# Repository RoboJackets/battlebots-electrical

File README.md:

BattleBots Electrical
=====================

Black Box Sensor
-----------
This folder has the design for a PCB that can measure kinematics during impact for testing combat robots.

Meltybrain
-----------
This folder contains the designs for PCBs for a combat robot that utilizes translational drift.

Motor Speed Testing
-------------------
This folder has code for graphing brushless motor spinup speed.

Safety LEDs
-----------
This folder has the design and code for a PCB for a safety LED controller for combat robots.

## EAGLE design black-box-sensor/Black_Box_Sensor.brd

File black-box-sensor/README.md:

Black-Box Sensor
=====================

This directory contains all design files for the Black-Box Sensor BattleBots project.  It is a sensor that will measure acceleration and jerk during collisions.

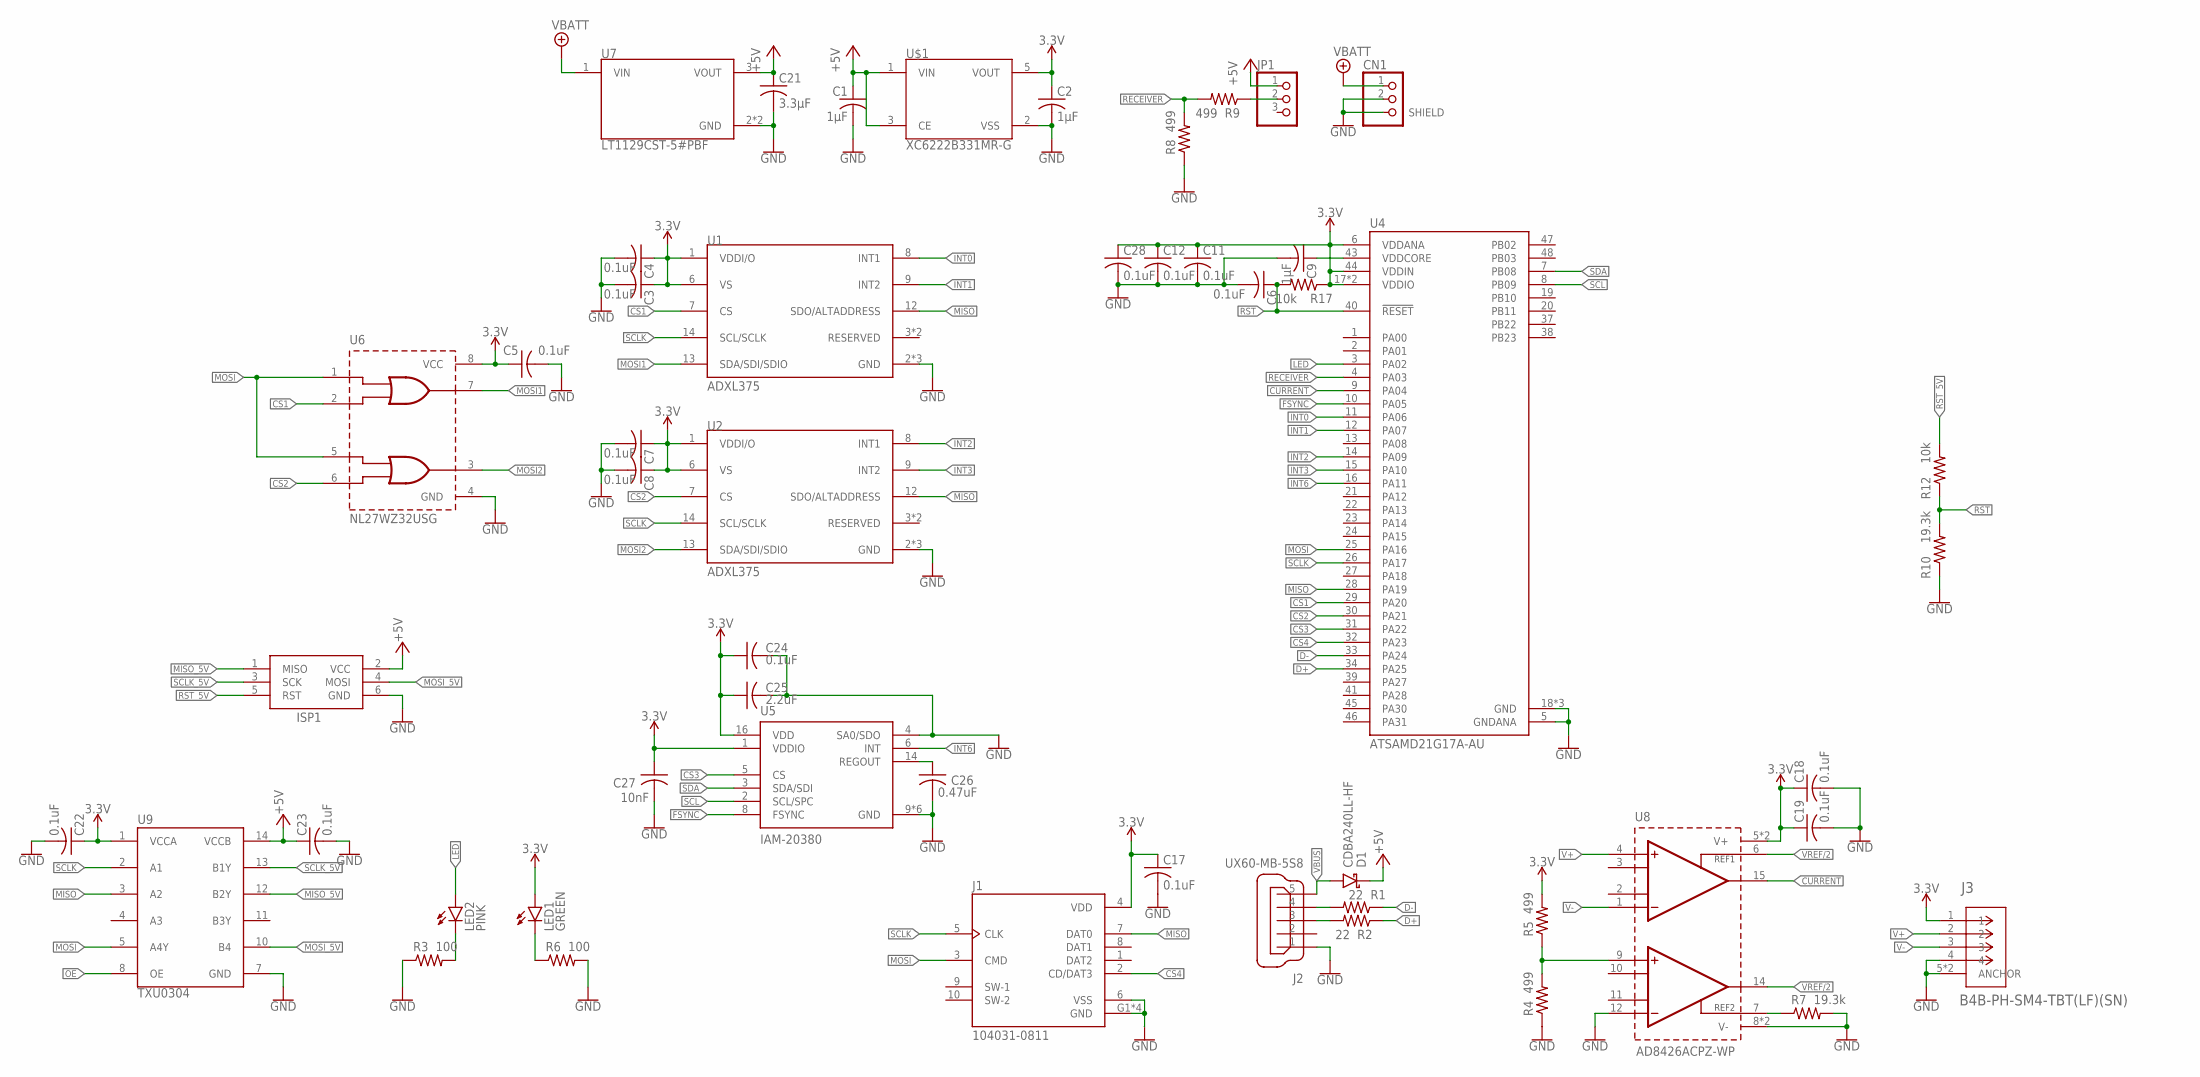
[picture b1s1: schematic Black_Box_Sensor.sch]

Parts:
C1, C2, C9: 1µF; C0603; VOLTAGE 10V
C3, C4, C5, C6, C7, C8, C11, C12, C17, C18, C19, C24, C28: 0.1uF; C0603
C21: 3.3µF; C0603; VOLTAGE 10V
C22, C23: 0.1uF; C0603K
C25: 2.2uF; C0603
C26: 0.47uF; C0603
C27: 10nF; C0603
CN1: JST_2PIN; JST-PH-2-SMT
D1: CDBA240LL-HF; DIOM5225X250N
ISP1: AVRISP-6; AVRISP
J1: 104031-0811; MOLEX_104031-0811
J2: UX60-MB-5S8
J3: B4B-PH-SM4-TBT(LF)(SN); CONN_B4B-PH-SM4-TB_JST
JP1: PINHD-1X3; 1X03
LED1: GREEN; CHIP-LED0805
LED2: PINK; KA-3528ASYC
R1, R2: 22; R0603
R3, R6: 100; R0603
R4, R5, R8, R9: 499; R0603
R7, R10: 19.3k; R0603
R12, R17: 10k; R0603
U1, U2: ADXL375; 14-VFLGA
U4: ATSAMD21G17A-AU; TQFP48
U5: IAM-20380; PQFN50P300X300X80-16N
U6: NL27WZ32USG; US8
U7: LT1129CST-5#PBF; SOT-223-3
U8: AD8426ACPZ-WP; 16LFCSP
U9: TXU0304; TSSOP14
U$1: XC6222B331MR-G; SOT-25

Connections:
3.3V: C2.1, C3.1, C4.1, C5.1, C7.1, C8.1, C11.1, C12.1, C17.1, C18.1, C19.1, C22.1, C24.1, C25.1, C27.1, C28.1, J1.4 (VDD), J3.1, LED1.A, R5.2, R17.1, U1.1 (VDDI/O), U1.6 (VS), U2.1 (VDDI/O), U2.6 (VS), U4.6 (VDDANA), U4.17 (VDDIO), U4.36 (VDDIO), U4.44 (VDDIN), U5.1 (VDDIO), U5.16 (VDD), U6.8 (VCC), U8.5 (V+), U8.16 (V+), U9.1 (VCCA), U$1.5 (VOUT)
+5V: C1.1, C21.1, C23.1, D1.C, JP1.1, U7.3 (VOUT), U9.14 (VCCB), U$1.1 (VIN), U$1.3 (CE)
CS1: U1.7 (CS), U4.29 (PA20), U6.2 (B1)
CS2: U2.7 (CS), U4.30 (PA21), U6.6 (B2)
CS3: U4.31 (PA22), U5.5 (CS)
CS4: J1.2 (CD/DAT3), U4.32 (PA23)
CURRENT: U4.9 (PA04), U8.15 (OUTA)
D+: R2.1, U4.34 (PA25)
D-: R1.1, U4.33 (PA24)
FSYNC: U4.10 (PA05), U5.8 (FSYNC)
GND: C1.2, C2.2, C3.2, C4.2, C5.2, C6.2, C7.2, C8.2, C9.2, C11.2, C12.2, C17.2, C18.2, C19.2, C21.2, C22.2, C23.2, C24.2, C25.2, C26.2, C27.2, C28.2, CN1.2, CN1.NC1 (SHIELD), CN1.NC2 (SHIELD), ISP1.6 (GND), J1.6 (VSS), J1.G1 (GND), J1.G2 (GND), J1.G3 (GND), J1.G4 (GND), J2.1, J3.4, J3.5 (ANCHOR), J3.6 (ANCHOR), R3.1, R4.1, R6.2, R7.2, R8.1, R10.1, U1.2 (GND), U1.4 (GND), U1.5 (GND), U2.2 (GND), U2.4 (GND), U2.5 (GND), U4.5 (GNDANA), U4.18 (GND), U4.35 (GND), U4.42 (GND), U5.4 (SA0/SDO), U5.9 (GND), U5.10 (GND), U5.11 (GND), U5.12 (GND), U5.13 (GND), U5.15 (GND), U6.4 (GND), U7.2 (GND), U7.4 (GND), U8.8 (V-), U8.12 (INB-), U8.13 (V-), U9.7 (GND), U$1.2 (VSS)
INT0: U1.8 (INT1), U4.11 (PA06)
INT1: U1.9 (INT2), U4.12 (PA07)
INT2: U2.8 (INT1), U4.14 (PA09)
INT3: U2.9 (INT2), U4.15 (PA10)
INT6: U4.16 (PA11), U5.6 (INT)
LED: LED2.A, U4.3 (PA02)
MISO: J1.7 (DAT0), U1.12 (SDO/ALTADDRESS), U2.12 (SDO/ALTADDRESS), U4.28 (PA19), U9.3 (A2)
MISO_5V: ISP1.1 (MISO), U9.12 (B2Y)
MOSI: J1.3 (CMD), U4.25 (PA16), U6.1 (A1), U6.5 (A2), U9.5 (A4Y)
MOSI1: U1.13 (SDA/SDI/SDIO), U6.7 (Y1)
MOSI2: U2.13 (SDA/SDI/SDIO), U6.3 (Y2)
MOSI_5V: ISP1.4 (MOSI), U9.10 (B4)
unnamed: C9.1, U4.43 (VDDCORE)
unnamed: J2.3, R2.2
unnamed: J2.4, R1.2
unnamed: R4.2, R5.1, U8.9 (INB+)
unnamed: LED2.C, R3.2
unnamed: LED1.C, R6.1
unnamed: JP1.2, R9.1
unnamed: R7.1, U8.7 (REFB)
unnamed: C26.1, U5.14 (REGOUT)
OE: U9.8 (OE)
RECEIVER: R8.2, R9.2, U4.4 (PA03)
RST: C6.1, R10.2, R12.1, R17.2, U4.40 (!RESET!)
RST_5V: ISP1.5 (RST), R12.2
SCL: U4.8 (PB09), U5.2 (SCL/SPC)
SCLK: J1.5 (CLK), U1.14 (SCL/SCLK), U2.14 (SCL/SCLK), U4.26 (PA17), U9.2 (A1)
SCLK_5V: ISP1.3 (SCK), U9.13 (B1Y)
SDA: U4.7 (PB08), U5.3 (SDA/SDI)
V+: J3.2, U8.4 (INA+)
V-: J3.3, U8.1 (INA-)
VBATT: CN1.1, U7.1 (VIN)
VBUS: D1.A, J2.5
VREF/2: U8.6 (REFA), U8.14 (OUTB)

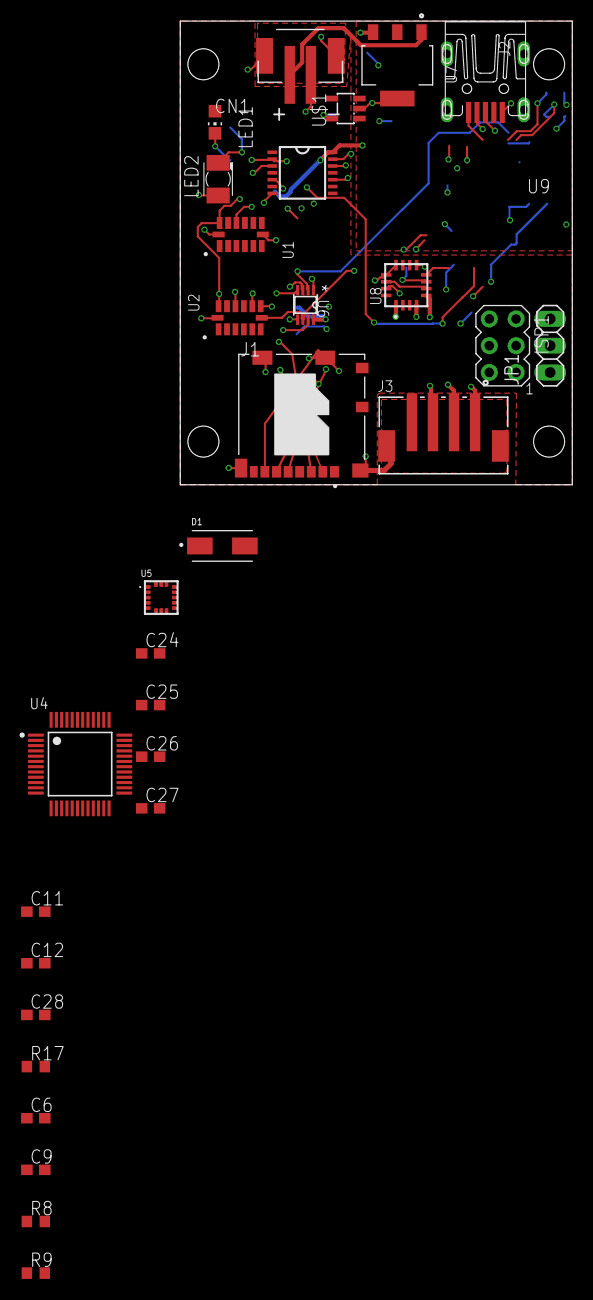
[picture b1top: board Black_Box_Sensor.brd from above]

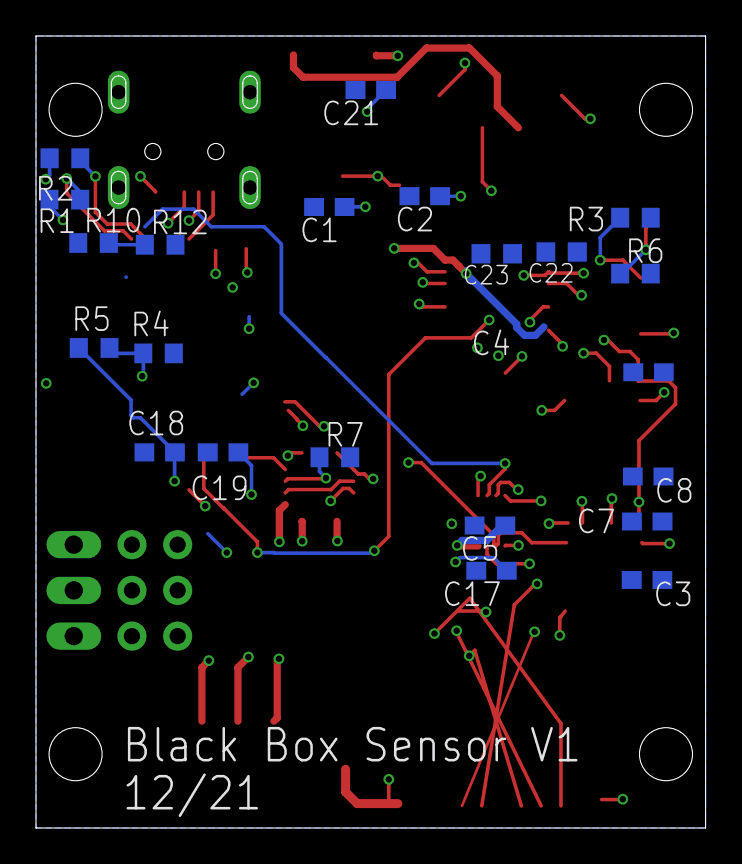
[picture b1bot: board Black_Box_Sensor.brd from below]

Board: 4 copper layers, 37.2 x 44.0 mm, 52 parts (22 on the bottom side), 44 nets.

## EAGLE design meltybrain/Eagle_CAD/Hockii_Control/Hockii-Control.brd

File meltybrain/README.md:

Meltybrain Electrical
=====================

This directory contains all design files for the Meltybrain battlebots project.  A Meltybrain is a robot design that uses translational drift (spinning quickly) to approximate  omnidirectional control.

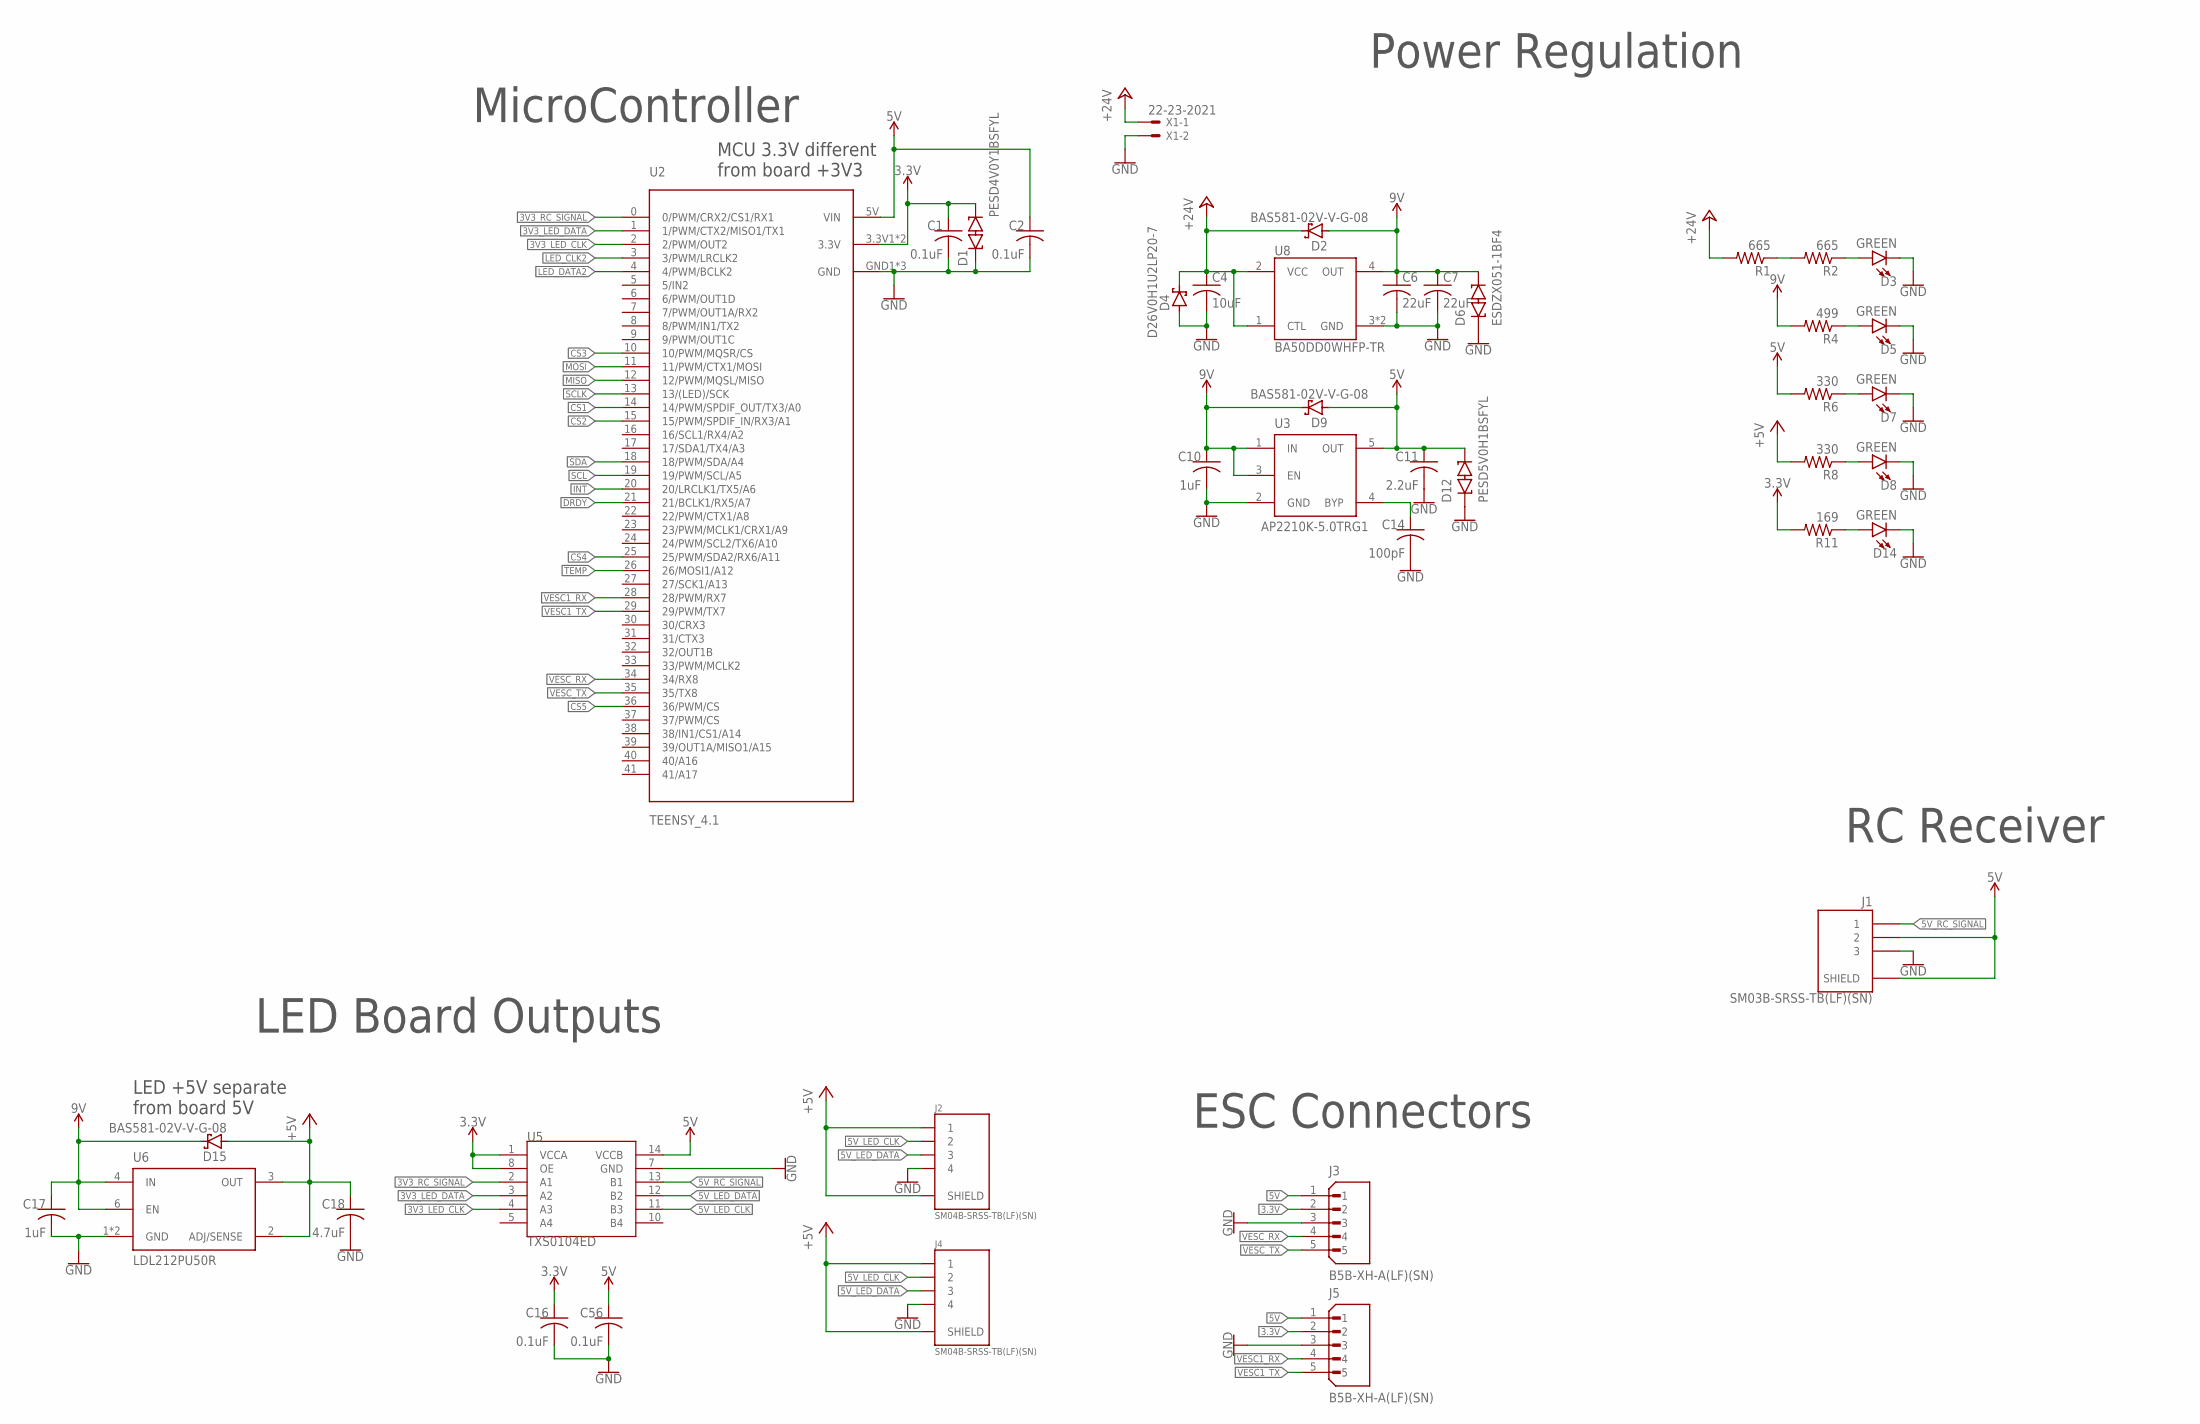
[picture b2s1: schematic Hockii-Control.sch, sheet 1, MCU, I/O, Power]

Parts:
C1, C2, C16, C56: 0.1uF; C0603
C4: 10uF; C1206
C6, C7: 22uF; C1206
C10, C17: 1uF; C0603
C11: 2.2uF; C0603
C14: 100pF; C0603
C18: 4.7uF; C0603
D1: PESD4V0Y1BSFYL; DSN0603-2
D2, D9, D15: BAS581-02V-V-G-08; SOD-523
D3, D5, D7, D8, D14: GREEN; LED-0603
D4: D26V0H1U2LP20-7
D6: ESDZX051-1BF4; DSN0603-2
D12: PESD5V0H1BSFYL; DSN0603-2
J1: SM03B-SRSS-TB(LF)(SN)
J2, J4: SM04B-SRSS-TB(LF)(SN)
J3, J5: B5B-XH-A(LF)(SN); JST_B5B-XH-A(LF)(SN)
R1, R2: 665; R0603
R4: 499; R0603
R6, R8: 330; R0603
R11: 169; R0603
U2: TEENSY_4.1
U3: AP2210K-5.0TRG1; SOT-23-5
U5: TXS0104ED; 14-SOIC
U6: LDL212PU50R; DFN6(3X3)
U8: BA50DD0WHFP-TR; HRP5
X1: 22-23-2021

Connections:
3.3V: C1.1, C16.1, D1.C2, J3.2, J5.2, R11.2, U2.3.3V1 (3.3V), U2.3.3V2 (3.3V), U5.1 (VCCA), U5.8 (OE); also elsewhere on the board
3V3_LED_CLK: U2.2 (2/PWM/OUT2), U5.4 (A3)
3V3_LED_DATA: U2.1 (1/PWM/CTX2/MISO1/TX1), U5.3 (A2)
3V3_RC_SIGNAL: U2.0 (0/PWM/CRX2/CS1/RX1), U5.2 (A1)
5V: C2.1, C11.1, C56.1, D9.2 (A), D12.C2, J1.2, J1.S1 (SHIELD), J1.S2 (SHIELD), J3.1, J5.1, R6.2, U2.5V (VIN), U3.5 (OUT), U5.14 (VCCB)
5V_LED_CLK: J2.2, J4.2, U5.11 (B3)
5V_LED_DATA: J2.3, J4.3, U5.12 (B2)
5V_RC_SIGNAL: J1.1, U5.13 (B1)
9V: C6.1, C7.1, C10.1, C17.1, D2.2 (A), D6.C2, D9.1 (C), D15.1 (C), R4.2, U3.1 (IN), U3.3 (EN), U6.4 (IN), U6.6 (EN), U8.4 (OUT)
+5V: C18.1, D15.2 (A), J2.1, J2.S1 (SHIELD), J2.S2 (SHIELD), J4.1, J4.S1 (SHIELD), J4.S2 (SHIELD), R8.2, U6.2 (ADJ/SENSE), U6.3 (OUT)
+24V: C4.1, D2.1 (C), D4.1 (C), R1.2, U8.1 (CTL), U8.2 (VCC), X1.1
CS1: U2.14 (14/PWM/SPDIF_OUT/TX3/A0); also elsewhere on the board
CS2: U2.15 (15/PWM/SPDIF_IN/RX3/A1); also elsewhere on the board
CS3: U2.10 (10/PWM/MQSR/CS); also elsewhere on the board
CS4: U2.25 (25/PWM/SDA2/RX6/A11); also elsewhere on the board
CS5: U2.36 (36/PWM/CS); also elsewhere on the board
DRDY: U2.21 (21/BCLK1/RX5/A7); also elsewhere on the board
GND: C1.2, C2.2, C4.2, C6.2, C7.2, C10.2, C11.2, C14.2, C16.2, C17.2, C18.2, C56.2, D1.C1, D3.C, D4.2 (A), D5.C, D6.C1, D7.C, D8.C, D12.C1, D14.C, J1.3, J2.4, J3.3, J4.4, J5.3, U2.GND1 (GND), U2.GND2 (GND), U2.GND3 (GND), U3.2 (GND), U5.7 (GND), U6.1 (GND), U6.7 (GND), U8.3 (GND), U8.6 (GND), X1.2; also elsewhere on the board
INT: U2.20 (20/LRCLK1/TX5/A6); also elsewhere on the board
LED_CLK2: U2.3 (3/PWM/LRCLK2)
LED_DATA2: U2.4 (4/PWM/BCLK2)
MISO: U2.12 (12/PWM/MQSL/MISO); also elsewhere on the board
MOSI: U2.11 (11/PWM/CTX1/MOSI); also elsewhere on the board
unnamed: C14.1, U3.4 (BYP)
unnamed: D8.A, R8.1
unnamed: D7.A, R6.1
unnamed: D5.A, R4.1
unnamed: D3.A, R2.1
unnamed: R1.1, R2.2
unnamed: D14.A, R11.1
SCL: U2.19 (19/PWM/SCL/A5); also elsewhere on the board
SCLK: U2.13 (13/(LED)/SCK); also elsewhere on the board
SDA: U2.18 (18/PWM/SDA/A4); also elsewhere on the board
TEMP: U2.26 (26/MOSI1/A12); also elsewhere on the board
VESC1_RX: J5.4, U2.28 (28/PWM/RX7)
VESC1_TX: J5.5, U2.29 (29/PWM/TX7)
VESC_RX: J3.4, U2.34 (34/RX8)
VESC_TX: J3.5, U2.35 (35/TX8)

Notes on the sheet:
MicroController
LED Board Outputs
Power Regulation
LED +5V separate from board 5V
RC Receiver
ESC Connectors
MCU 3.3V different from board +3V3

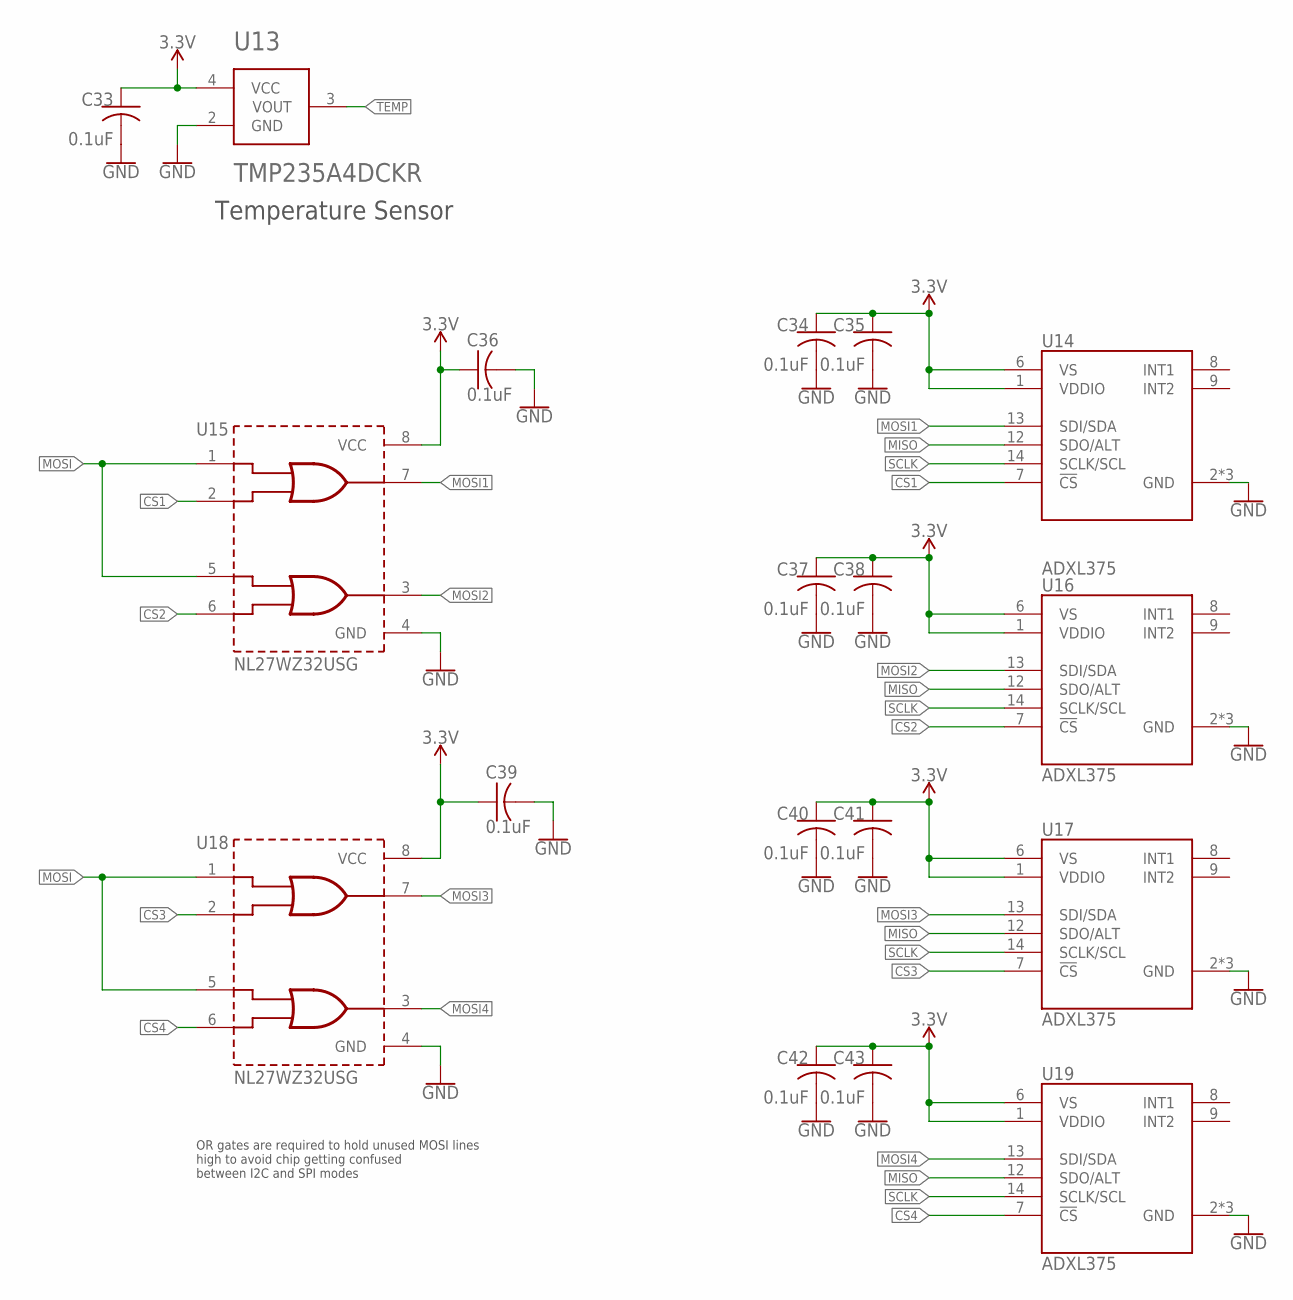
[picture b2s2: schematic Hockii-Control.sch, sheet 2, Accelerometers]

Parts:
C33, C34, C35, C36, C37, C38, C39, C40, C41, C42, C43: 0.1uF; C0603
U13: TMP235A4DCKR; SOT-353
U14, U16, U17, U19: ADXL375; 14-LGA
U15, U18: NL27WZ32USG; US8

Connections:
3.3V: C33.1, C34.1, C35.1, C36.1, C37.1, C38.1, C39.1, C40.1, C41.1, C42.1, C43.1, U13.4 (VCC), U14.1 (VDDIO), U14.6 (VS), U15.8 (VCC), U16.1 (VDDIO), U16.6 (VS), U17.1 (VDDIO), U17.6 (VS), U18.8 (VCC), U19.1 (VDDIO), U19.6 (VS); also elsewhere on the board
CS1: U14.7 (!CS), U15.2 (B1); also elsewhere on the board
CS2: U15.6 (B2), U16.7 (!CS); also elsewhere on the board
CS3: U17.7 (!CS), U18.2 (B1); also elsewhere on the board
CS4: U18.6 (B2), U19.7 (!CS); also elsewhere on the board
GND: C33.2, C34.2, C35.2, C36.2, C37.2, C38.2, C39.2, C40.2, C41.2, C42.2, C43.2, U13.2 (GND), U14.2 (GND), U14.4 (GND), U14.5 (GND), U15.4 (GND), U16.2 (GND), U16.4 (GND), U16.5 (GND), U17.2 (GND), U17.4 (GND), U17.5 (GND), U18.4 (GND), U19.2 (GND), U19.4 (GND), U19.5 (GND); also elsewhere on the board
MISO: U14.12 (SDO/ALT), U16.12 (SDO/ALT), U17.12 (SDO/ALT), U19.12 (SDO/ALT); also elsewhere on the board
MOSI: U15.1 (A1), U15.5 (A2), U18.1 (A1), U18.5 (A2); also elsewhere on the board
MOSI1: U14.13 (SDI/SDA), U15.7 (Y1)
MOSI2: U15.3 (Y2), U16.13 (SDI/SDA)
MOSI3: U17.13 (SDI/SDA), U18.7 (Y1)
MOSI4: U18.3 (Y2), U19.13 (SDI/SDA)
SCLK: U14.14 (SCLK/SCL), U16.14 (SCLK/SCL), U17.14 (SCLK/SCL), U19.14 (SCLK/SCL); also elsewhere on the board
TEMP: U13.3 (VOUT); also elsewhere on the board

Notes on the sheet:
OR gates are required to hold unused MOSI lines high to avoid chip getting confused between I2C and SPI modes
Temperature Sensor

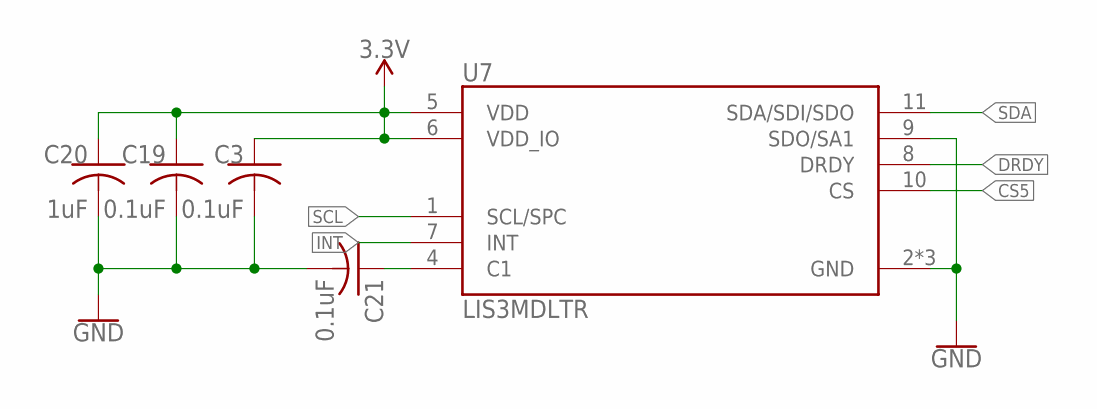
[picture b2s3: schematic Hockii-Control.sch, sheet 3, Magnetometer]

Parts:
C3, C19, C21: 0.1uF; C0603
C20: 1uF; C0603
U7: LIS3MDLTR; LGA-12_2X2X1_STM

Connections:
3.3V: C3.1, C19.1, C20.1, U7.5 (VDD), U7.6 (VDD_IO); also elsewhere on the board
CS5: U7.10 (CS); also elsewhere on the board
DRDY: U7.8 (DRDY); also elsewhere on the board
GND: C3.2, C19.2, C20.2, C21.2, U7.2 (GND), U7.3 (GND), U7.9 (SDO/SA1), U7.12 (GND); also elsewhere on the board
INT: U7.7 (INT); also elsewhere on the board
unnamed: C21.1, U7.4 (C1)
SCL: U7.1 (SCL/SPC); also elsewhere on the board
SDA: U7.11 (SDA/SDI/SDO); also elsewhere on the board

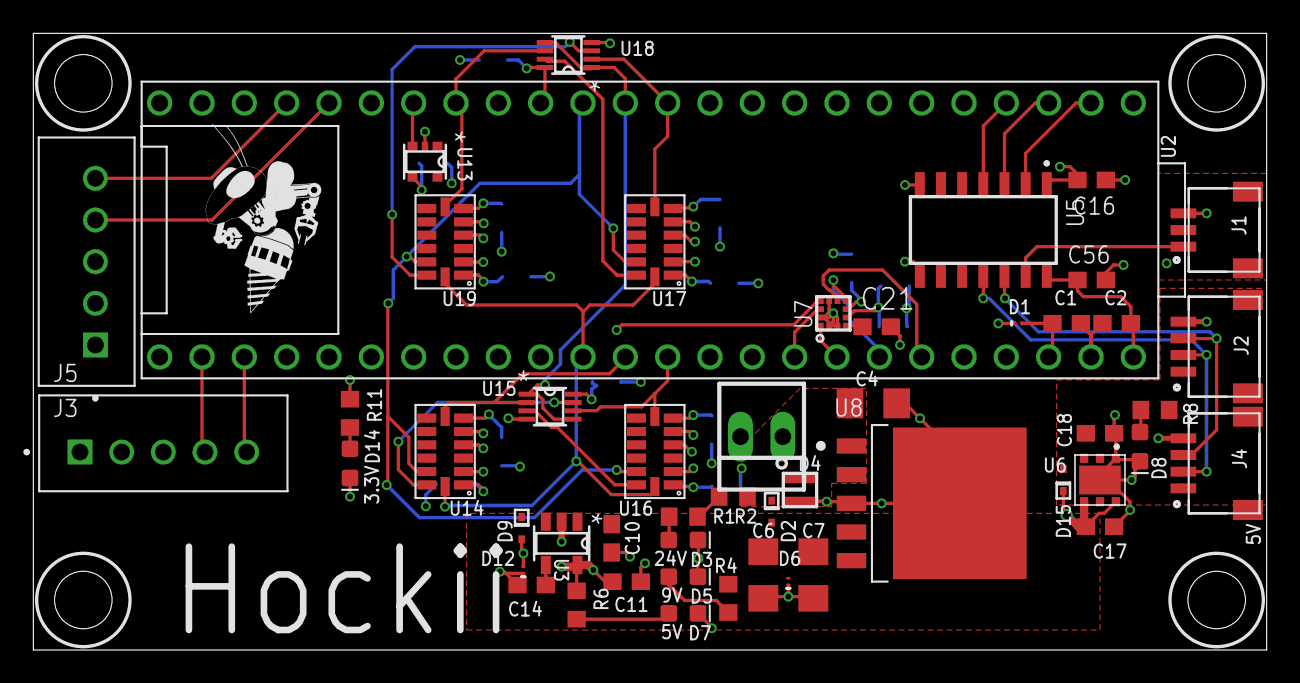
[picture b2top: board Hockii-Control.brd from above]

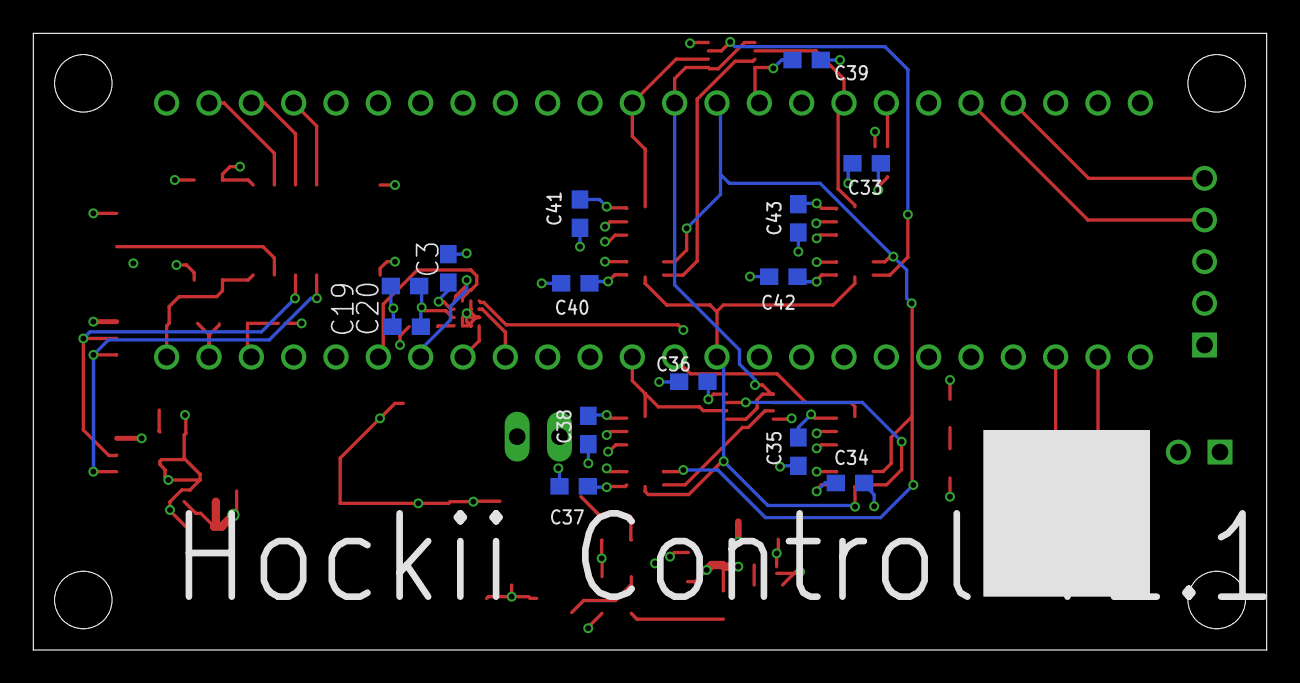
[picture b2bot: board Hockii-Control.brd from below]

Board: 4 copper layers, 74.0 x 37.0 mm, 65 parts (14 on the bottom side), 41 nets.

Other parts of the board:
U$2: ROBOBUZZ_0.6X

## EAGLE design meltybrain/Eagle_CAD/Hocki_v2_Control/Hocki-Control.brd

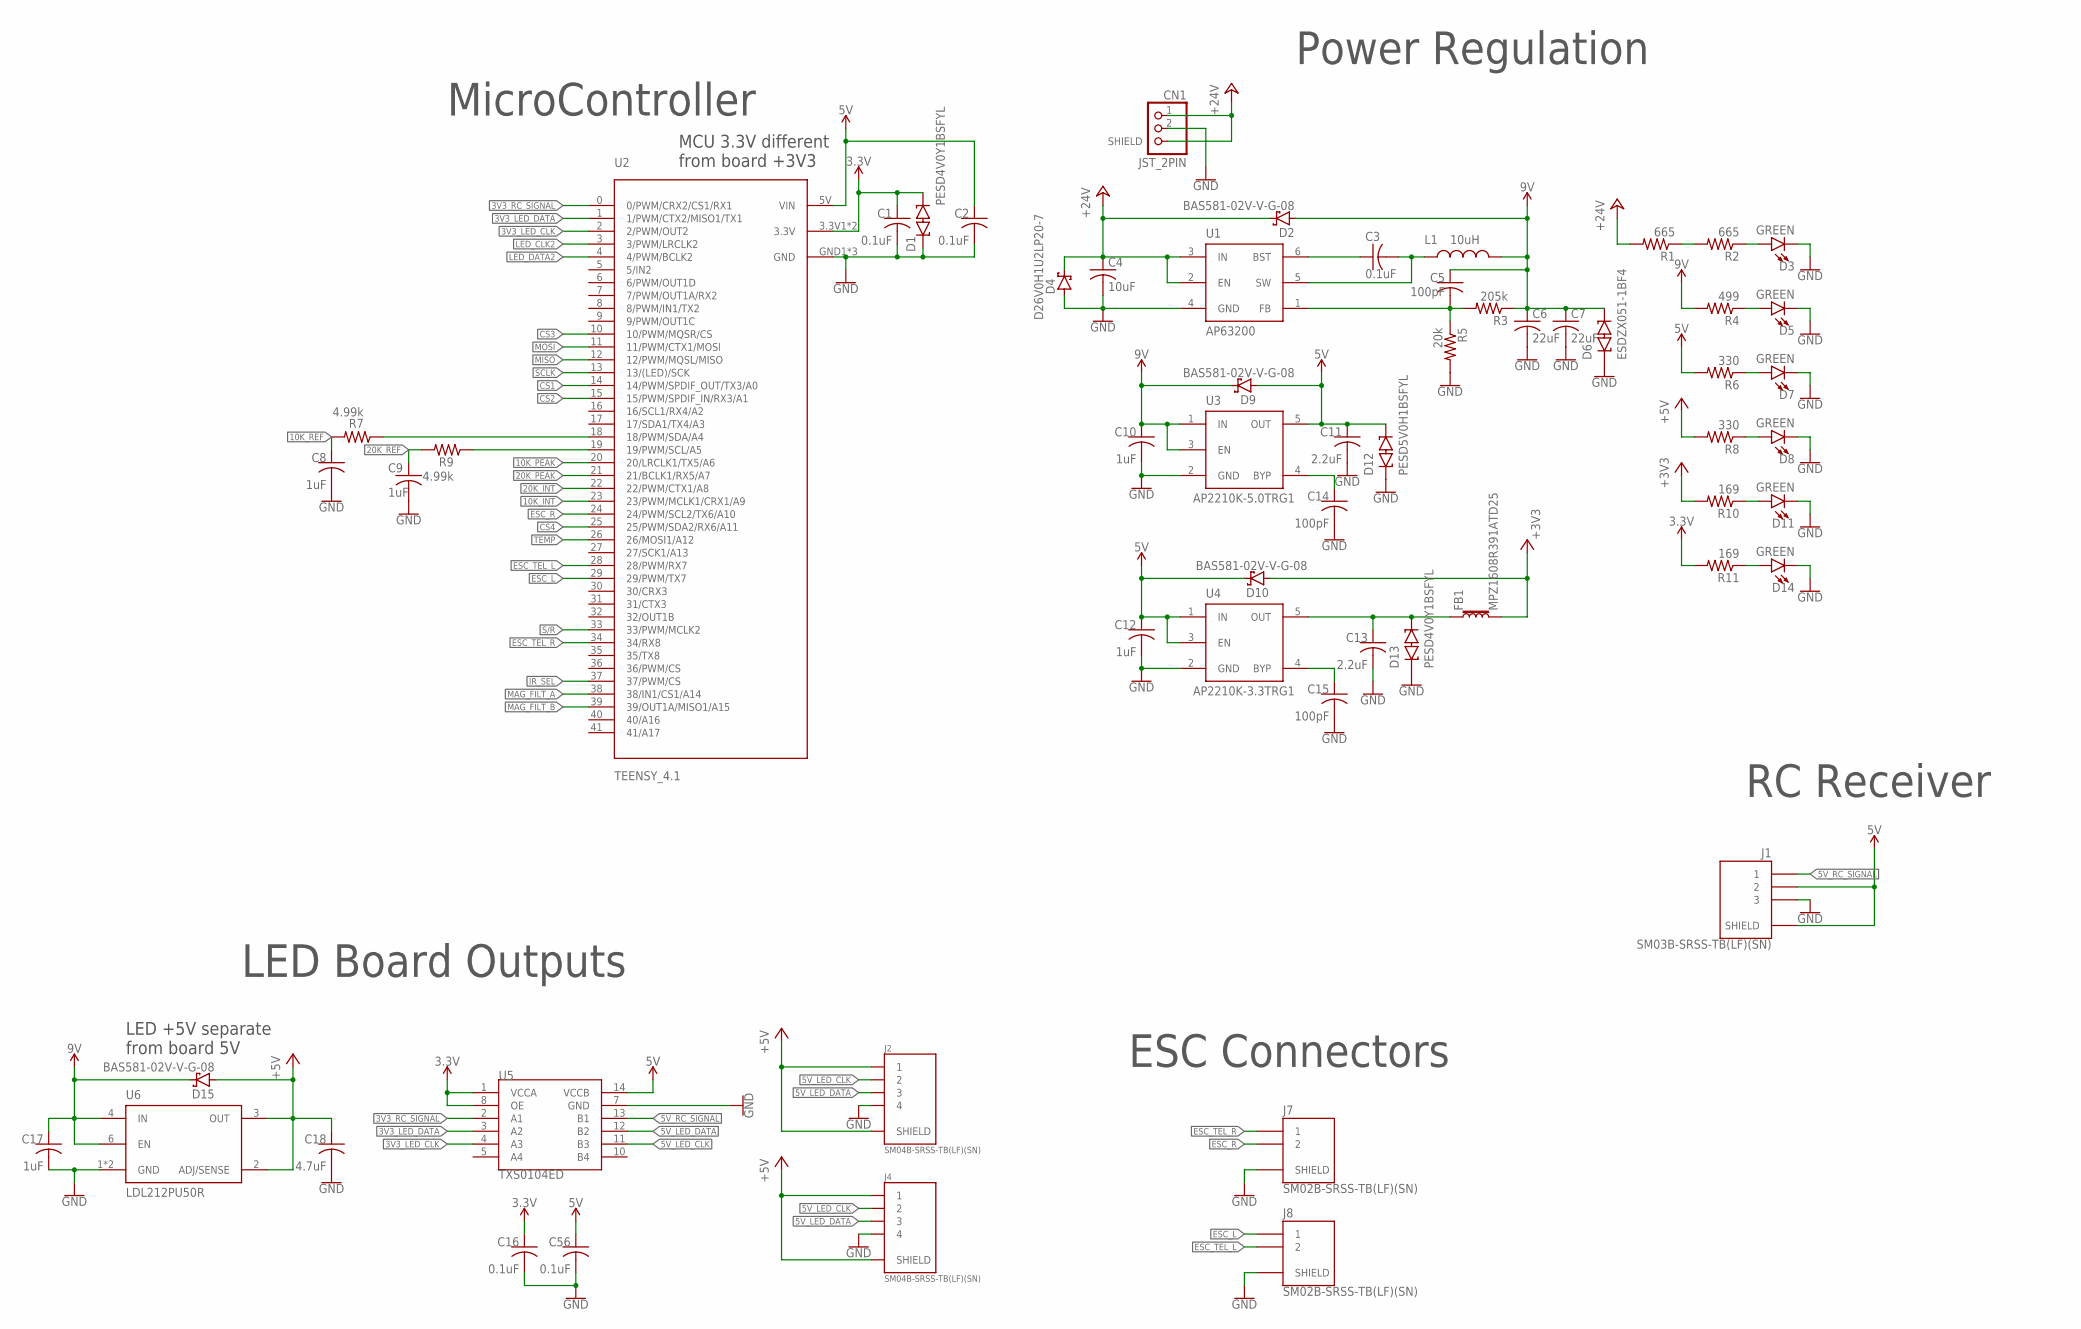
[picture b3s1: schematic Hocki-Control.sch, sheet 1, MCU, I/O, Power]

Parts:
C1, C2, C3, C16, C56: 0.1uF; C0603
C4: 10uF; C1206
C5, C14, C15: 100pF; C0603
C6, C7: 22uF; C1206
C8, C9, C10, C12, C17: 1uF; C0603
C11, C13: 2.2uF; C0603
C18: 4.7uF; C0603
CN1: JST_2PIN; JST-PH-2-SMT
D1, D13: PESD4V0Y1BSFYL; DSN0603-2
D2, D9, D10, D15: BAS581-02V-V-G-08; SOD-523
D3, D5, D7, D8, D11, D14: GREEN; LED-0603
D4: D26V0H1U2LP20-7
D6: ESDZX051-1BF4; DSN0603-2
D12: PESD5V0H1BSFYL; DSN0603-2
FB1: MPZ1608R391ATD25; 0603
J1: SM03B-SRSS-TB(LF)(SN)
J2, J4: SM04B-SRSS-TB(LF)(SN)
J7, J8: SM02B-SRSS-TB(LF)(SN)
L1: 10uH; LQH5BPN100M38L
R1, R2: 665; R0603
R3: 205k; R0603
R4: 499; R0603
R5: 20k; R0603
R6, R8: 330; R0603
R7, R9: 4.99k; R0603
R10, R11: 169; R0603
U1: AP63200; SOT-23-6
U2: TEENSY_4.1
U3: AP2210K-5.0TRG1; SOT-23-5
U4: AP2210K-3.3TRG1; SOT-23-5
U5: TXS0104ED; 14-SOIC
U6: LDL212PU50R; DFN6(3X3)

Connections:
3.3V: C1.1, C16.1, D1.C2, R11.2, U2.3.3V1 (3.3V), U2.3.3V2 (3.3V), U5.1 (VCCA), U5.8 (OE); also elsewhere on the board
3V3_LED_CLK: U2.2 (2/PWM/OUT2), U5.4 (A3)
3V3_LED_DATA: U2.1 (1/PWM/CTX2/MISO1/TX1), U5.3 (A2)
3V3_RC_SIGNAL: U2.0 (0/PWM/CRX2/CS1/RX1), U5.2 (A1)
5V: C2.1, C11.1, C12.1, C56.1, D9.2 (A), D10.1 (C), D12.C2, J1.2, J1.S1 (SHIELD), J1.S2 (SHIELD), R6.2, U2.5V (VIN), U3.5 (OUT), U4.1 (IN), U4.3 (EN), U5.14 (VCCB); also elsewhere on the board
5V_LED_CLK: J2.2, J4.2, U5.11 (B3)
5V_LED_DATA: J2.3, J4.3, U5.12 (B2)
5V_RC_SIGNAL: J1.1, U5.13 (B1)
9V: C5.1, C6.1, C7.1, C10.1, C17.1, D2.2 (A), D6.C2, D9.1 (C), D15.1 (C), L1.2, R3.1, R4.2, U3.1 (IN), U3.3 (EN), U6.4 (IN), U6.6 (EN); also elsewhere on the board
10K_INT: U2.23 (23/PWM/MCLK1/CRX1/A9); also elsewhere on the board
10K_PEAK: U2.20 (20/LRCLK1/TX5/A6); also elsewhere on the board
10K_REF: C8.1, R7.2; also elsewhere on the board
20K_INT: U2.22 (22/PWM/CTX1/A8); also elsewhere on the board
20K_PEAK: U2.21 (21/BCLK1/RX5/A7); also elsewhere on the board
20K_REF: C9.1, R9.2; also elsewhere on the board
+3V3: D10.2 (A), FB1.2, R10.2; also elsewhere on the board
+5V: C18.1, D15.2 (A), J2.1, J2.S1 (SHIELD), J2.S2 (SHIELD), J4.1, J4.S1 (SHIELD), J4.S2 (SHIELD), R8.2, U6.2 (ADJ/SENSE), U6.3 (OUT)
+24V: C4.1, CN1.1, CN1.NC1 (SHIELD), CN1.NC2 (SHIELD), D2.1 (C), D4.1 (C), R1.2, U1.2 (EN), U1.3 (IN)
CS1: U2.14 (14/PWM/SPDIF_OUT/TX3/A0); also elsewhere on the board
CS2: U2.15 (15/PWM/SPDIF_IN/RX3/A1); also elsewhere on the board
CS3: U2.10 (10/PWM/MQSR/CS); also elsewhere on the board
CS4: U2.25 (25/PWM/SDA2/RX6/A11); also elsewhere on the board
ESC_L: J8.1, U2.29 (29/PWM/TX7)
ESC_R: J7.2, U2.24 (24/PWM/SCL2/TX6/A10)
ESC_TEL_L: J8.2, U2.28 (28/PWM/RX7)
ESC_TEL_R: J7.1, U2.34 (34/RX8)
GND: C1.2, C2.2, C4.2, C6.2, C7.2, C8.2, C9.2, C10.2, C11.2, C12.2, C13.2, C14.2, C15.2, C16.2, C17.2, C18.2, C56.2, CN1.2, D1.C1, D3.C, D4.2 (A), D5.C, D6.C1, D7.C, D8.C, D11.C, D12.C1, D13.C1, D14.C, J1.3, J2.4, J4.4, J7.S1 (SHIELD), J7.S2 (SHIELD), J8.S1 (SHIELD), J8.S2 (SHIELD), R5.2, U1.4 (GND), U2.GND1 (GND), U2.GND2 (GND), U2.GND3 (GND), U3.2 (GND), U4.2 (GND), U5.7 (GND), U6.1 (GND), U6.7 (GND); also elsewhere on the board
IR_SEL: U2.37 (37/PWM/CS); also elsewhere on the board
LED_CLK2: U2.3 (3/PWM/LRCLK2)
LED_DATA2: U2.4 (4/PWM/BCLK2)
MAG_FILT_A: U2.38 (38/IN1/CS1/A14); also elsewhere on the board
MAG_FILT_B: U2.39 (39/OUT1A/MISO1/A15); also elsewhere on the board
MISO: U2.12 (12/PWM/MQSL/MISO); also elsewhere on the board
MOSI: U2.11 (11/PWM/CTX1/MOSI); also elsewhere on the board
unnamed: C3.1, U1.6 (BST)
unnamed: C3.2, L1.1, U1.5 (SW)
unnamed: C14.1, U3.4 (BYP)
unnamed: C15.1, U4.4 (BYP)
unnamed: C5.2, R3.2, R5.1, U1.1 (FB)
unnamed: D8.A, R8.1
unnamed: D7.A, R6.1
unnamed: D11.A, R10.1
unnamed: D5.A, R4.1
unnamed: D3.A, R2.1
unnamed: R1.1, R2.2
unnamed: R7.1, U2.18 (18/PWM/SDA/A4)
unnamed: R9.1, U2.19 (19/PWM/SCL/A5)
unnamed: D14.A, R11.1
unnamed: C13.1, D13.C2, FB1.1, U4.5 (OUT)
S/R: U2.33 (33/PWM/MCLK2); also elsewhere on the board
SCLK: U2.13 (13/(LED)/SCK); also elsewhere on the board
TEMP: U2.26 (26/MOSI1/A12); also elsewhere on the board

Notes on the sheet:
MicroController
LED Board Outputs
Power Regulation
LED +5V separate from board 5V
RC Receiver
ESC Connectors
MCU 3.3V different from board +3V3

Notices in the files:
parts and their libraries:
SparkFun-PowerSymbols: Licensing: Creative Commons ShareAlike 4.0 International - https://creativecommons.org/licenses/by-sa/4.0
